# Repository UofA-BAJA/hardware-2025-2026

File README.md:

# hardware-2025-2026
Hardware Branch for 2025-2026 Baja

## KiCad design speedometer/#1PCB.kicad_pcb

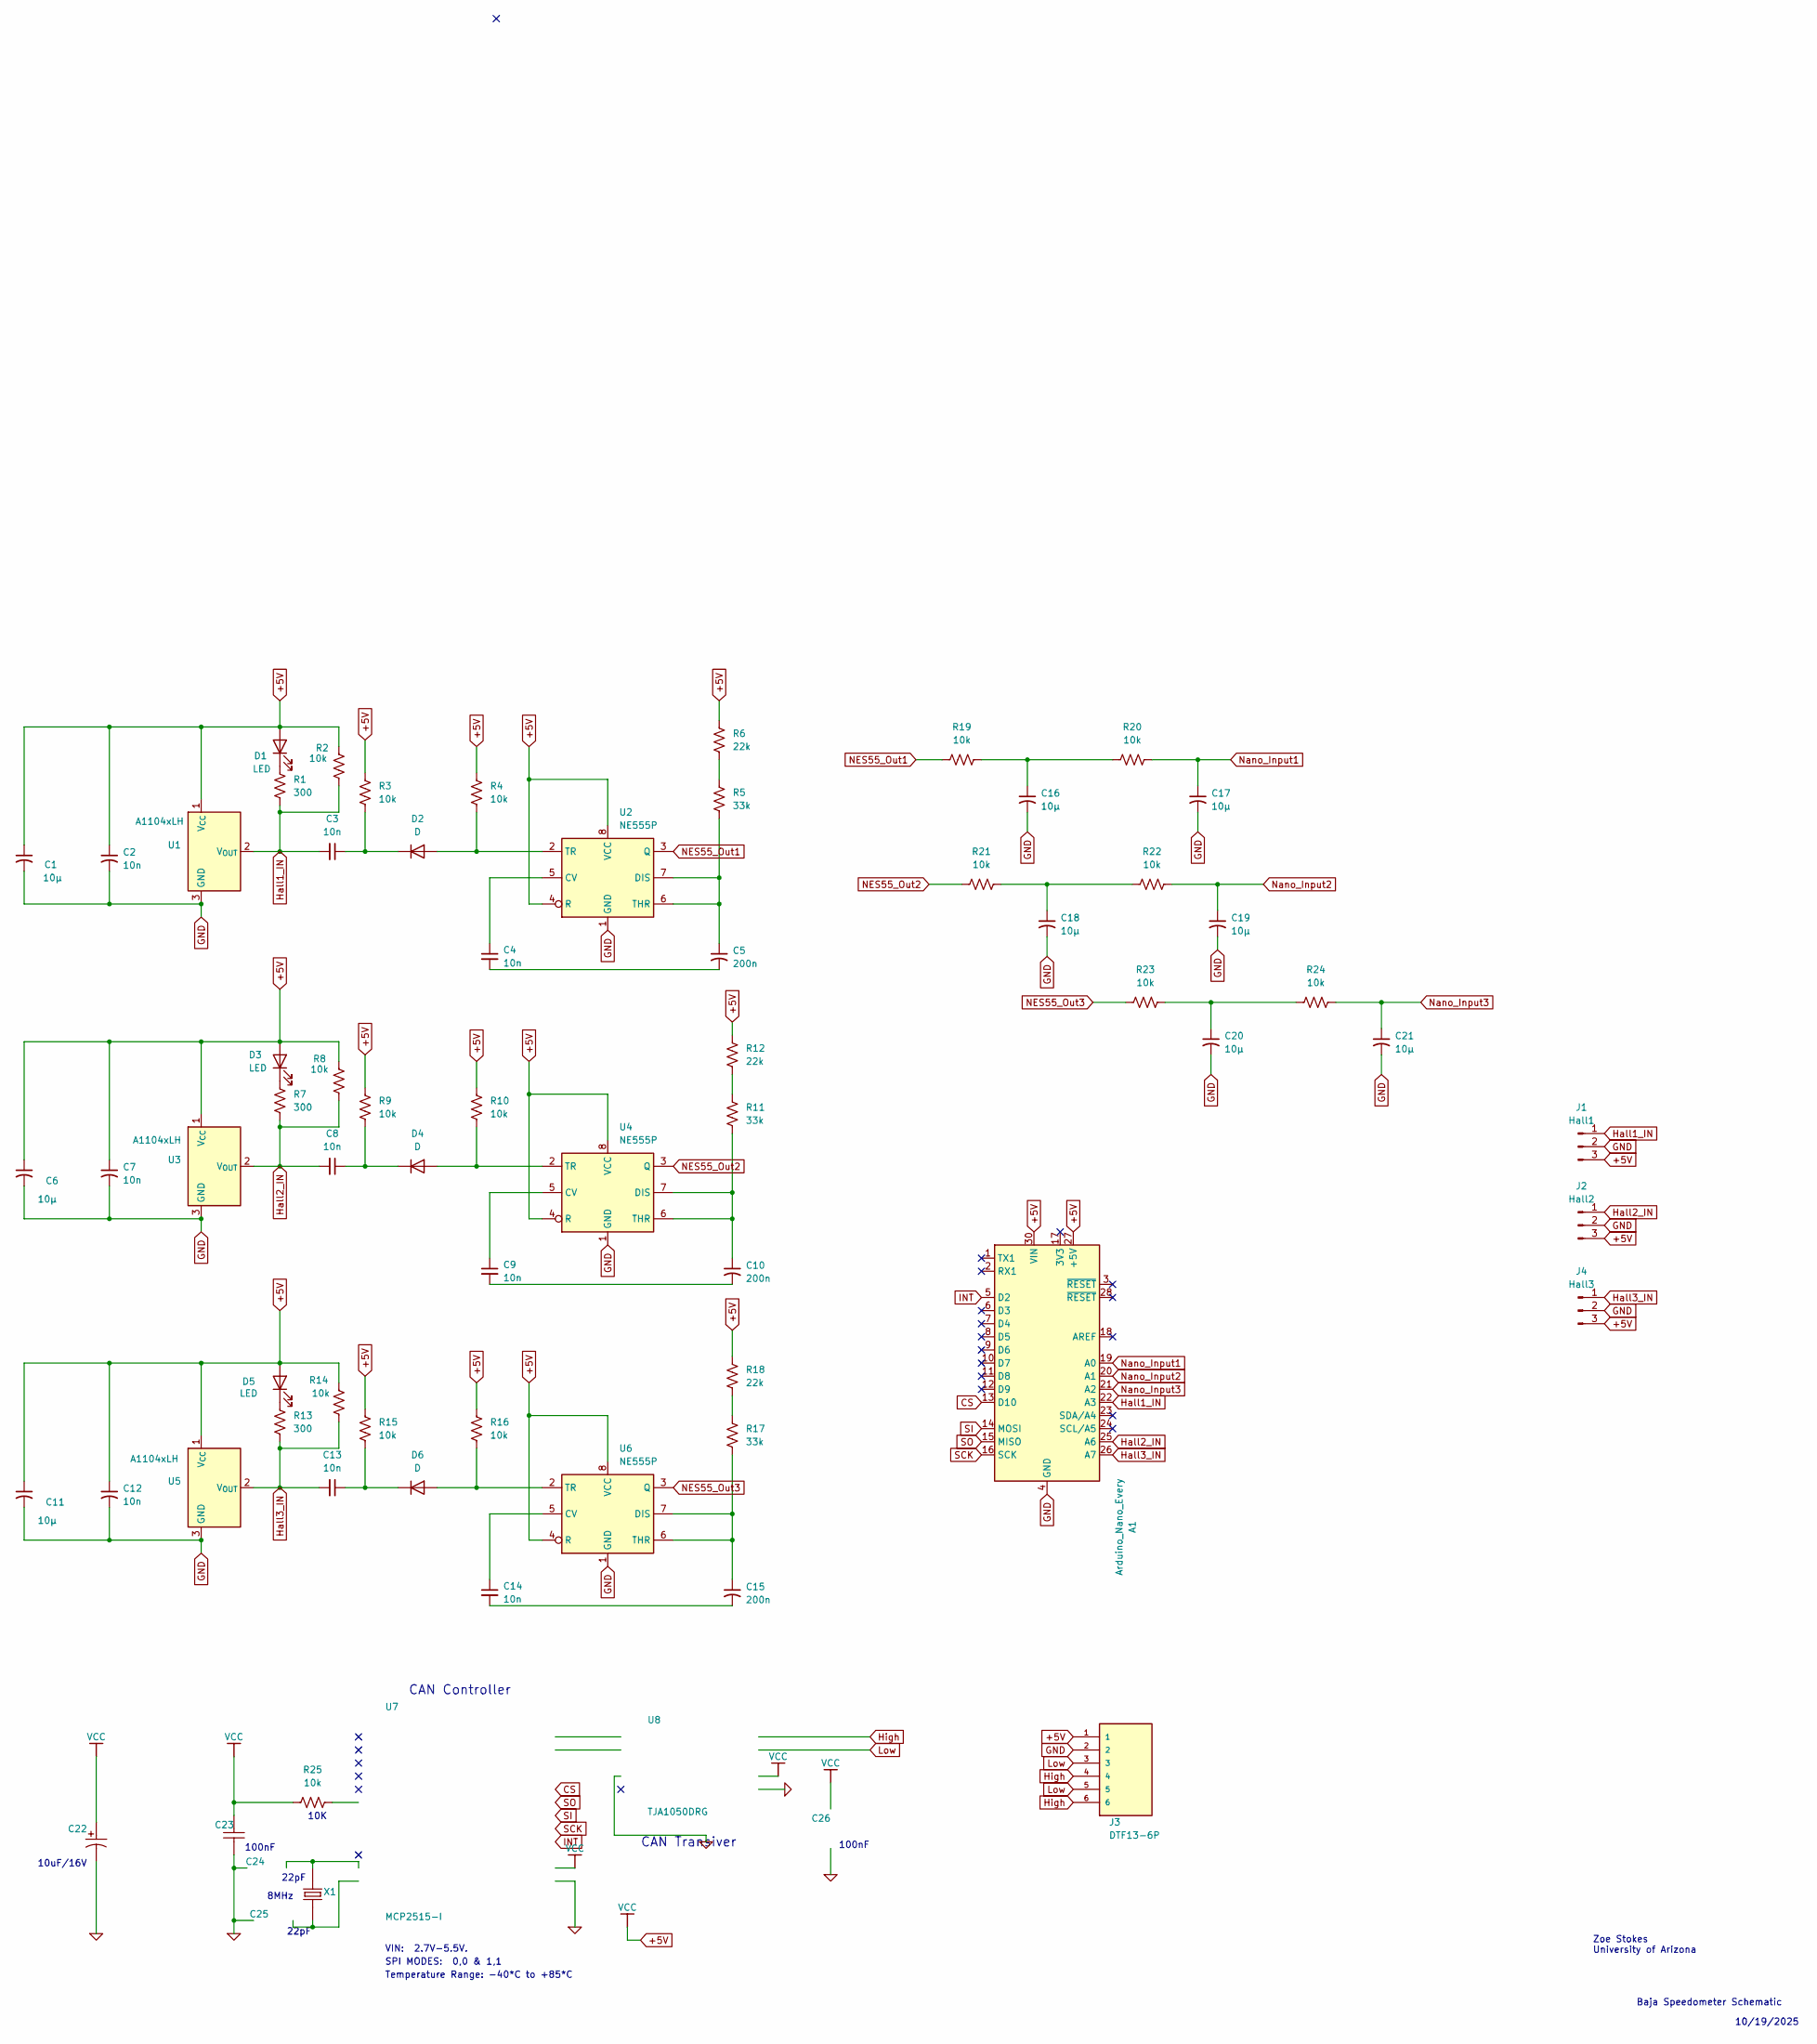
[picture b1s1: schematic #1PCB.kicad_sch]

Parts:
A1: Arduino_Nano_Every; Arduino_Nano
C1, C6, C11, C16, C17, C18, C19, C20, C21: 10µ; CP_Radial_D4.0mm_P2.00mm
C2, C7, C12: 10n; CP_Radial_D4.0mm_P2.00mm
C3, C4, C8, C9, C13, C14: 10n; C_Disc_D3.8mm_W2.6mm_P2.50mm
C5, C10, C15: 200n; CP_Radial_D4.0mm_P2.00mm
C22: 10uF/16V; CP_EIA-1608-08_AVX-J
C23, C26: 100nF; C_0603_1608Metric; PART NUMBER C0603-N.C.
C24, C25: 22pF; C_0603_1608Metric; PART NUMBER C0603-N.C.
D1, D3, D5: LED; LED_D4.0mm
D2, D4, D6: D; D_DO-41_SOD81_P7.62mm_Horizontal
J1: Hall1; PinHeader_1x03_P2.54mm_Vertical
J2: Hall2; PinHeader_1x03_P2.54mm_Vertical
J3: DTF13-6P; TE_DTF13-6P; PARTREV B
J4: Hall3; PinHeader_1x03_P2.54mm_Vertical
R1, R7, R13: 300; R_Axial_DIN0204_L3.6mm_D1.6mm_P7.62mm_Horizontal
R2, R3, R4, R8, R9, R10, R14, R15, R16, R19, R20, R21, R22, R23, R24, R25: 10k; R_Axial_DIN0204_L3.6mm_D1.6mm_P7.62mm_Horizontal
R5, R11, R17: 33k; R_Axial_DIN0204_L3.6mm_D1.6mm_P7.62mm_Horizontal
R6, R12, R18: 22k; R_Axial_DIN0204_L3.6mm_D1.6mm_P7.62mm_Horizontal
U1, U3, U5: A1104xLH; SOT-23W
U2, U4, U6: NE555P; DIP-8_W7.62mm
U7: MCP2515-I; SOIC-18W_7.5x11.6mm_P1.27mm; MANUFACTURER PART MCP2515-I; JLCPCB PART CLASS Extended Part
U8: TJA1050DRG; SOIC-8_5.3x5.3mm_P1.27mm; MANUFACTURER PART TJA1050DRG; LCSC PART NAME TJA1050DRG
X1: 8MHz; Crystal_SMD_HC49-SD

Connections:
0: C22.2, C23.1, C24.2, C25.2, C26.1, U7.9 (VSS), U8.2 (GND), U8.8 (STB)
+5V: A1.27 (+5V), A1.30 (VIN), C1.1, C2.1, C6.1, C7.1, C11.1, C12.1, C22.1, C23.2, C26.2, D1.2 (A), D3.2 (A), D5.2 (A), J1.3, J2.3, J3.1, J4.3, R2.1, R3.1, R4.1, R6.1, R8.1, R9.1, R10.1, R12.1, R14.1, R15.1, R16.1, R18.1, R25.1, U1.1 (V_{CC}), U2.4 (R), U2.8 (VCC), U3.1 (V_{CC}), U4.4 (R), U4.8 (VCC), U5.1 (V_{CC}), U6.4 (R), U6.8 (VCC), U7.18 (VDD), U8.3 (VCC)
CS: A1.13 (D10), U7.16 (~CS)
GND: A1.4 (GND), A1.29 (GND), C1.2, C2.2, C6.2, C7.2, C11.2, C12.2, C16.2, C17.2, C18.2, C19.2, C20.2, C21.2, J1.2, J2.2, J3.2, J4.2, U1.3 (GND), U2.1 (GND), U3.3 (GND), U4.1 (GND), U5.3 (GND), U6.1 (GND)
Hall1_IN: A1.22 (A3), C3.2, J1.1, R1.2, R2.2, U1.2 (V_{OUT})
Hall2_IN: A1.25 (A6), C8.2, J2.1, R7.2, R8.2, U3.2 (V_{OUT})
Hall3_IN: A1.26 (A7), C13.2, J4.1, R13.2, R14.2, U5.2 (V_{OUT})
High: J3.4, J3.6, U8.7 (CANH)
INT: A1.5 (D2), U7.12 (~INT)
Low: J3.3, J3.5, U8.6 (CANL)
NES55_Out1: R19.2, U2.3 (Q)
NES55_Out2: R21.2, U4.3 (Q)
NES55_Out3: R23.2, U6.3 (Q)
Nano_Input1: A1.19 (A0), C17.1, R20.1
Nano_Input2: A1.20 (A1), C19.1, R22.1
Nano_Input3: A1.21 (A2), C21.1, R24.1
unnamed: C4.2, C5.2
unnamed: C9.2, C10.2
unnamed: C14.2, C15.2
unnamed: C16.1, R19.1, R20.2
unnamed: C18.1, R21.1, R22.2
unnamed: C20.1, R23.1, R24.2
unnamed: D1.1 (K), R1.1
unnamed: D2.2 (A), R4.2, U2.2 (TR)
unnamed: C3.1, D2.1 (K), R3.2
unnamed: D3.1 (K), R7.1
unnamed: D4.2 (A), R10.2, U4.2 (TR)
unnamed: C8.1, D4.1 (K), R9.2
unnamed: D5.1 (K), R13.1
unnamed: D6.2 (A), R16.2, U6.2 (TR)
unnamed: C13.1, D6.1 (K), R15.2
unnamed: R5.1, R6.2
unnamed: R11.1, R12.2
unnamed: R17.1, R18.2
unnamed: C4.1, U2.5 (CV)
unnamed: C5.1, R5.2, U2.6 (THR), U2.7 (DIS)
unnamed: C9.1, U4.5 (CV)
unnamed: C10.1, R11.2, U4.6 (THR), U4.7 (DIS)
unnamed: C14.1, U6.5 (CV)
unnamed: C15.1, R17.2, U6.6 (THR), U6.7 (DIS)
unnamed: C25.1, U7.8 (OSC1), X1.1
unnamed: C24.1, U7.7 (OSC2), X1.2
unnamed: U7.2 (RXCAN), U8.4 (RXD)
unnamed: U7.1 (TXCAN), U8.1 (TXD)
unnamed: R25.2, U7.17 (~RESET)
SCK: A1.16 (SCK), U7.13 (SCK)
SI: A1.14 (MOSI), U7.14 (SI)
SO: A1.15 (MISO), U7.15 (SO)

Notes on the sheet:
Zoe Stokes University of Arizona
100nF
Baja Speedometer Schematic
VIN: 2.7V-5.5V.
22pF
CAN Controller
10K
10/19/2025
CAN Transiver
8MHz
Temperature Range: -40*C to +85*C
SPI MODES: 0,0 & 1,1
10uF/16V

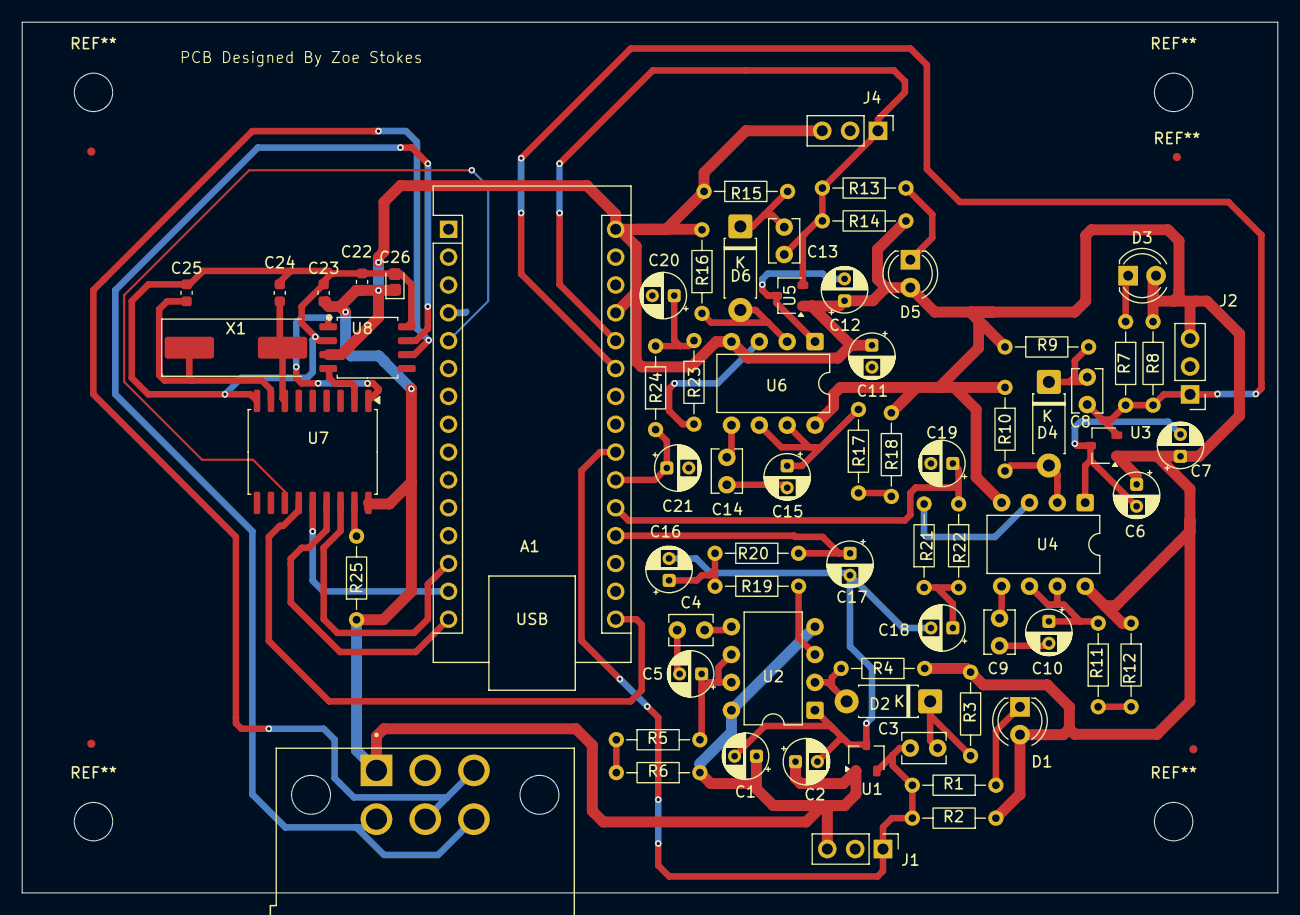
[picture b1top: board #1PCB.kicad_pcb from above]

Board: 2 copper layers, 114.5 x 79.4 mm, 71 parts (0 on the bottom side), 48 nets.

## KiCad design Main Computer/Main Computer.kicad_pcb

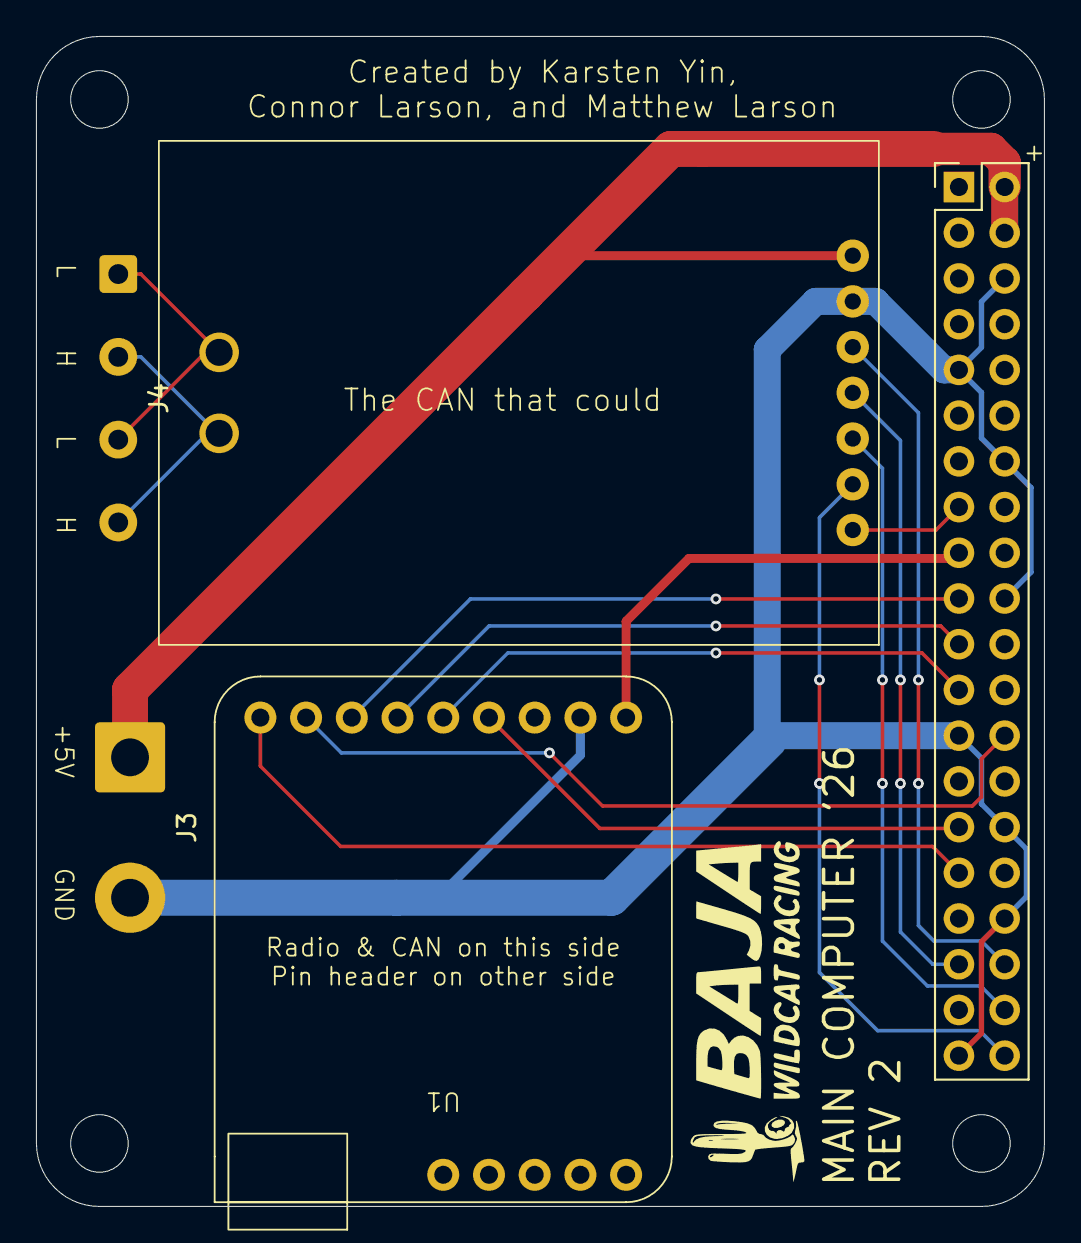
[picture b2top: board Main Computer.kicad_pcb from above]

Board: 2 copper layers, 56.0 x 65.0 mm, 5 parts (0 on the bottom side), 16 nets.

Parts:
J1: Pi 5 GPIO HEADER; PinHeader_2x20_P2.54mm_Vertical
J3: Conn_01x02; SolderWire-1.5sqmm_1x02_P7.8mm_D1.7mm_OD3.9mm
J4: CAN to outer connector; SolderWire-0.5sqmm_1x04_P4.6mm_D0.9mm_OD2.1mm
U1: RFM9X Breakout; Adafruit RFM95W Breakout
UNIT_1: HiLetgo CAN Bus; HiLetgo CAN Bus (Facing Up)

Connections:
3V3: J1.17 (3V3), U1.1 (VIN)
+5v: J1.2 (5V), J1.4 (5V), J3.1, UNIT_1.7 (VCC)
CAN_CS: J1.36 (GPIO_16), UNIT_1.5 (CS)
CAN_INT: J1.15 (GPIO_22), UNIT_1.1 (INT)
CSN: J1.26 (GPIO_7), U1.8 (CS)
GND: J1.6 (GND), J1.9 (GND), J1.14 (GND), J1.20 (GND), J1.25 (GND), J1.30 (GND), J1.34 (GND), J1.39 (GND), J3.2, U1.2 (GND), UNIT_1.6 (GND)
High: J4.2, J4.4, UNIT_1.8 (High_CAN)
Low: J4.1, J4.3, UNIT_1.9 (Low_CAN)
RADIO_INT: J1.29 (GPIO_5), U1.4 (G0_INT)
RST: J1.31 (GPIO_6), U1.9 (RST)
SCK: J1.23 (GPIO_11), U1.5 (SCK)
SI: J1.19 (GPIO_10), U1.7 (MOSI)
SO: J1.21 (GPIO_9), U1.6 (MISO)
SPI1_MISO: J1.35 (GPIO_19), UNIT_1.4 (SO)
SPI1_MOSI: J1.38 (GPIO_20), UNIT_1.3 (SI)
SPI1_SCK: J1.40 (GPIO_21), UNIT_1.2 (SCK)

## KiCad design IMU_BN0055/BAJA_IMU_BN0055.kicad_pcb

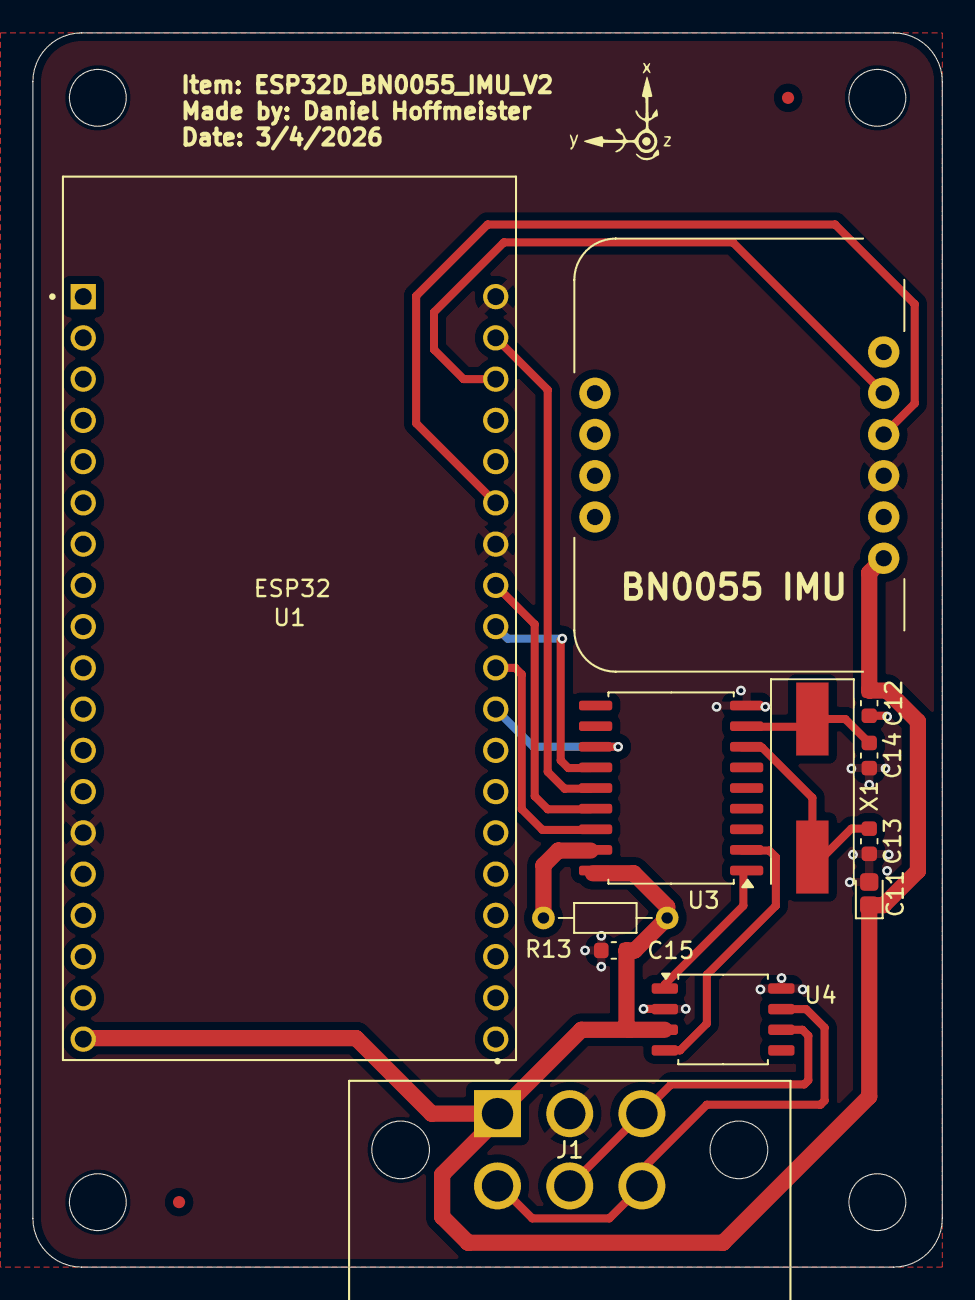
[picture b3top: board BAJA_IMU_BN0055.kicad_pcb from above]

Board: 2 copper layers, 56.0 x 76.0 mm, 12 parts (0 on the bottom side), 16 nets.

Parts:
C11: 10uF/16V; CP_EIA-1608-08_AVX-J
C12, C15: 100nF; C_0603_1608Metric
C13, C14: 22pF; C_0603_1608Metric
J1: DTF13-6P; TE_DTF13-6P
R13: 10k; R_Axial_DIN0204_L3.6mm_D1.6mm_P7.62mm_Horizontal
U1: ESP32-DEVKITC-32D; MODULE_ESP32-DEVKITC-32D
U3: MCP2515-I; SOIC-18W_7.5x11.6mm_P1.27mm
U4: TJA1050DRG; SOIC-8_5.3x5.3mm_P1.27mm
UNIT_1: BNO055; MODULE_2472(BN0055)
X1: 8MHz; Crystal_SMD_HC49-SD

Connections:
0: C11.2, C12.1, C13.2, C14.2, C15.1, J1.2, U1.J2-14 (GND1), U1.J3-1 (GND3), U1.J3-7 (GND2), U3.9 (VSS), U4.2 (GND), U4.8 (STB), UNIT_1.3 (GND)
+5V: C11.1, C12.2, C15.2, J1.1, R13.1, U1.J2-19 (EXT_5V), U3.18 (VDD), U4.3 (VCC), UNIT_1.1 (VIN)
CS: U1.J3-10 (IO5), U3.16 (~CS)
High: J1.4, J1.6, U4.7 (CANH)
Int: U1.J3-11 (IO17), U3.12 (~INT)
Low: J1.3, J1.5, U4.6 (CANL)
unnamed: U1.J3-6 (IO21), UNIT_1.4 (SDA)
unnamed: U1.J3-3 (IO22), UNIT_1.5 (SCL)
unnamed: C14.1, U3.8 (OSC1), X1.1
unnamed: C13.1, U3.7 (OSC2), X1.2
unnamed: U3.2 (RXCAN), U4.4 (RXD)
unnamed: U3.1 (TXCAN), U4.1 (TXD)
unnamed: R13.2, U3.17 (~RESET)
SCK: U1.J3-9 (IO18), U3.13 (SCK)
SI: U1.J3-2 (IO23), U3.14 (SI)
SO: U1.J3-8 (IO19), U3.15 (SO)

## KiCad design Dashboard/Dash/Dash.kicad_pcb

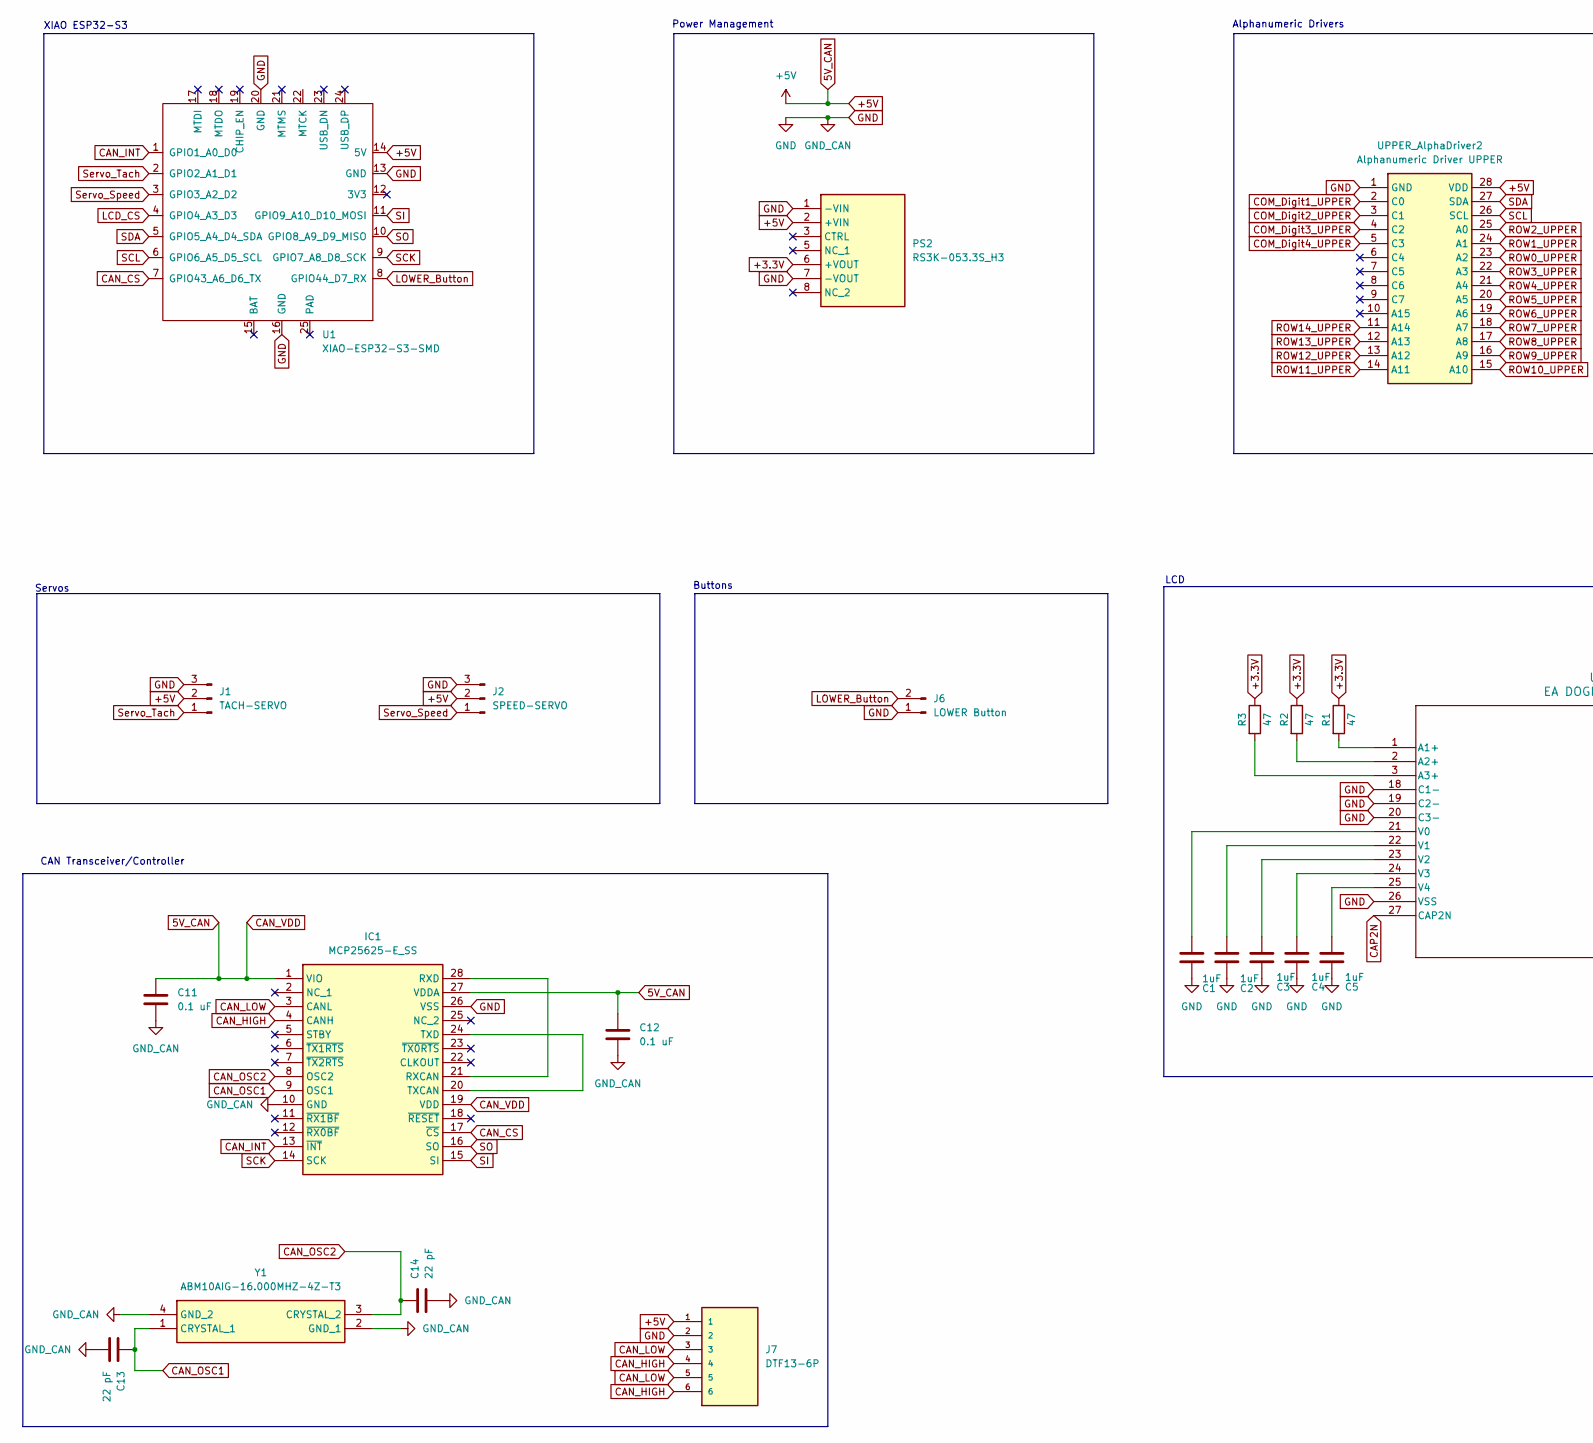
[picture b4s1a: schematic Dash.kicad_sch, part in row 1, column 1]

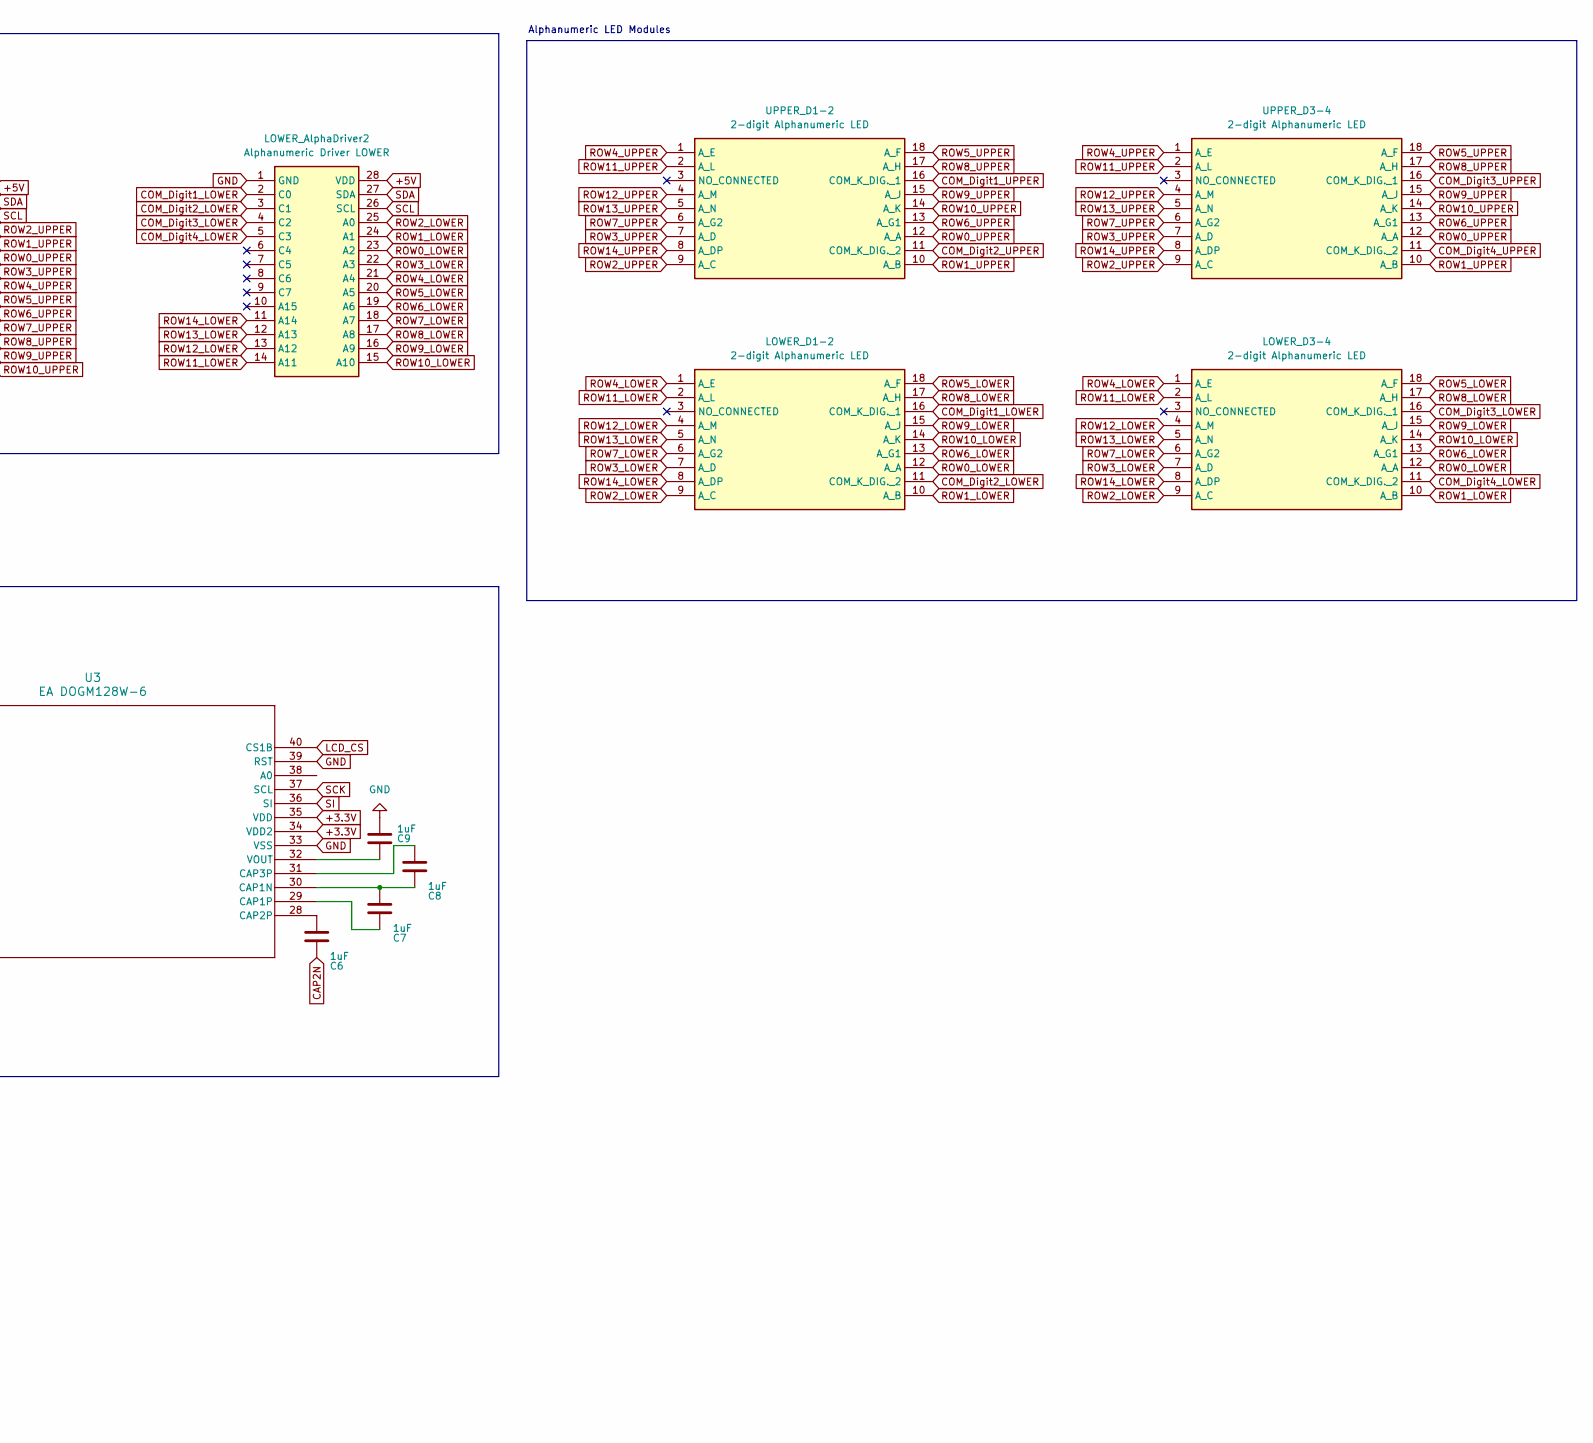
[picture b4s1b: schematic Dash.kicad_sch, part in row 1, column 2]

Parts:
C1, C2, C3, C4, C5, C6, C7, C8, C9: 1uF; CAPC1608X90
C11, C12: 0.1 uF; CAPC0603X35N
C13, C14: 22 pF; CAPC1608X87N
IC1: MCP25625-E_SS; SOP65P780X200-28N; Manufacturer_Part_Number MCP25625-E/SS; Mouser Part Number 579-MCP25625-E/SS
J1: TACH-SERVO; PinHeader_1x03_P2.54mm_Vertical
J2: SPEED-SERVO; PinHeader_1x03_P2.54mm_Vertical
J6: LOWER Button; PinHeader_1x02_P2.54mm_Vertical
J7: DTF13-6P; TE_DTF13-6P; PARTREV B
LOWER_AlphaDriver2: Alphanumeric Driver LOWER; DIP1778W100P254L3556H630Q28N; Manufacturer_Part_Number 1427; Mouser Part Number 485-1427
LOWER_D1-2, LOWER_D3-4: 2-digit Alphanumeric LED; 1908; Manufacturer_Part_Number 1908; Mouser Part Number 485-1908
PS2: RS3K-053.3S_H3; RS3K0533SH3; Manufacturer_Part_Number RS3K-053.3S/H3; Mouser Part Number 919-RS3K-053.3S/H3
R1, R2, R3: 47; RESC2012X65N
U1: XIAO-ESP32-S3-SMD; XIAO-ESP32S3-SMD
U3: EA DOGM128W-6; EA_DOGM128-6
UPPER_AlphaDriver2: Alphanumeric Driver UPPER; DIP1778W100P254L3556H630Q28N; Manufacturer_Part_Number 1427; Mouser Part Number 485-1427
UPPER_D1-2, UPPER_D3-4: 2-digit Alphanumeric LED; 1908; Manufacturer_Part_Number 1908; Mouser Part Number 485-1908
Y1: ABM10AIG-16.000MHZ-4Z-T3; ABM10AIG16000MHZ4ZT3; Manufacturer_Part_Number ABM10AIG-16.000MHZ-4Z-T3; Mouser Part Number 815-M10AIG-16-4ZT3

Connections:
+3.3V: PS2.6 (+VOUT), R1.1, R2.1, R3.1, U3.34 (VDD2), U3.35 (VDD)
+5V: C11.1, C12.1, IC1.1 (VIO), IC1.19 (VDD), IC1.27 (VDDA), J1.2, J2.2, J7.1, LOWER_AlphaDriver2.28 (VDD), PS2.2 (+VIN), U1.14 (5V), UPPER_AlphaDriver2.28 (VDD); also elsewhere on the board
CAN_CS: IC1.17 (~CS), U1.7 (GPIO43_A6_D6_TX)
CAN_HIGH: IC1.4 (CANH), J7.4, J7.6
CAN_INT: IC1.13 (~INT), U1.1 (GPIO1_A0_D0)
CAN_LOW: IC1.3 (CANL), J7.3, J7.5
CAN_OSC1: C13.1, IC1.9 (OSC1), Y1.1 (CRYSTAL_1)
CAN_OSC2: C14.1, IC1.8 (OSC2), Y1.3 (CRYSTAL_2)
CAP2N: C6.1, U3.27 (CAP2N)
COM_Digit1_LOWER: LOWER_AlphaDriver2.2 (C0), LOWER_D1-2.16 (COM_K_DIG._1); also elsewhere on the board
COM_Digit1_UPPER: UPPER_AlphaDriver2.2 (C0), UPPER_D1-2.16 (COM_K_DIG._1); also elsewhere on the board
COM_Digit2_LOWER: LOWER_AlphaDriver2.3 (C1), LOWER_D1-2.11 (COM_K_DIG._2); also elsewhere on the board
COM_Digit2_UPPER: UPPER_AlphaDriver2.3 (C1), UPPER_D1-2.11 (COM_K_DIG._2); also elsewhere on the board
COM_Digit3_LOWER: LOWER_AlphaDriver2.4 (C2), LOWER_D3-4.16 (COM_K_DIG._1); also elsewhere on the board
COM_Digit3_UPPER: UPPER_AlphaDriver2.4 (C2), UPPER_D3-4.16 (COM_K_DIG._1); also elsewhere on the board
COM_Digit4_LOWER: LOWER_AlphaDriver2.5 (C3), LOWER_D3-4.11 (COM_K_DIG._2); also elsewhere on the board
COM_Digit4_UPPER: UPPER_AlphaDriver2.5 (C3), UPPER_D3-4.11 (COM_K_DIG._2); also elsewhere on the board
GND: C1.1, C2.1, C3.1, C4.1, C5.1, C9.2, C11.2, C12.2, C13.2, C14.2, IC1.10 (GND), IC1.26 (VSS), J1.3, J2.3, J6.1, J7.2, LOWER_AlphaDriver2.1 (GND), PS2.1 (-VIN), PS2.7 (-VOUT), U1.13 (GND), U1.16 (GND), U1.20 (GND), U3.18 (C1-), U3.19 (C2-), U3.20 (C3-), U3.26 (VSS), U3.33 (VSS), U3.39 (RST), UPPER_AlphaDriver2.1 (GND), Y1.2 (GND_1), Y1.4 (GND_2); also elsewhere on the board
LCD_CS: U1.4 (GPIO4_A3_D3), U3.40 (CS1B)
LOWER_Button: J6.2, U1.8 (GPIO44_D7_RX)
unnamed: IC1.21 (RXCAN), IC1.28 (RXD)
unnamed: IC1.20 (TXCAN), IC1.24 (TXD)
unnamed: R1.2, U3.1 (A1+)
unnamed: R2.2, U3.2 (A2+)
unnamed: R3.2, U3.3 (A3+)
unnamed: C7.2, C8.1, U3.30 (CAP1N)
unnamed: C7.1, U3.29 (CAP1P)
unnamed: C6.2, U3.28 (CAP2P)
unnamed: C8.2, U3.31 (CAP3P)
unnamed: C1.2, U3.21 (V0)
unnamed: C2.2, U3.22 (V1)
unnamed: C3.2, U3.23 (V2)
unnamed: C4.2, U3.24 (V3)
unnamed: C5.2, U3.25 (V4)
unnamed: C9.1, U3.32 (VOUT)
ROW0_LOWER: LOWER_AlphaDriver2.23 (A2), LOWER_D1-2.12 (A_A), LOWER_D3-4.12 (A_A); also elsewhere on the board
ROW0_UPPER: UPPER_AlphaDriver2.23 (A2), UPPER_D1-2.12 (A_A), UPPER_D3-4.12 (A_A); also elsewhere on the board
ROW1_LOWER: LOWER_AlphaDriver2.24 (A1), LOWER_D1-2.10 (A_B), LOWER_D3-4.10 (A_B); also elsewhere on the board
ROW1_UPPER: UPPER_AlphaDriver2.24 (A1), UPPER_D1-2.10 (A_B), UPPER_D3-4.10 (A_B); also elsewhere on the board
ROW2_LOWER: LOWER_AlphaDriver2.25 (A0), LOWER_D1-2.9 (A_C), LOWER_D3-4.9 (A_C); also elsewhere on the board
ROW2_UPPER: UPPER_AlphaDriver2.25 (A0), UPPER_D1-2.9 (A_C), UPPER_D3-4.9 (A_C); also elsewhere on the board
ROW3_LOWER: LOWER_AlphaDriver2.22 (A3), LOWER_D1-2.7 (A_D), LOWER_D3-4.7 (A_D); also elsewhere on the board
ROW3_UPPER: UPPER_AlphaDriver2.22 (A3), UPPER_D1-2.7 (A_D), UPPER_D3-4.7 (A_D); also elsewhere on the board
ROW4_LOWER: LOWER_AlphaDriver2.21 (A4), LOWER_D1-2.1 (A_E), LOWER_D3-4.1 (A_E); also elsewhere on the board
ROW4_UPPER: UPPER_AlphaDriver2.21 (A4), UPPER_D1-2.1 (A_E), UPPER_D3-4.1 (A_E); also elsewhere on the board
ROW5_LOWER: LOWER_AlphaDriver2.20 (A5), LOWER_D1-2.18 (A_F), LOWER_D3-4.18 (A_F); also elsewhere on the board
ROW5_UPPER: UPPER_AlphaDriver2.20 (A5), UPPER_D1-2.18 (A_F), UPPER_D3-4.18 (A_F); also elsewhere on the board
ROW6_LOWER: LOWER_AlphaDriver2.19 (A6), LOWER_D1-2.13 (A_G1), LOWER_D3-4.13 (A_G1); also elsewhere on the board
ROW6_UPPER: UPPER_AlphaDriver2.19 (A6), UPPER_D1-2.13 (A_G1), UPPER_D3-4.13 (A_G1); also elsewhere on the board
ROW7_LOWER: LOWER_AlphaDriver2.18 (A7), LOWER_D1-2.6 (A_G2), LOWER_D3-4.6 (A_G2); also elsewhere on the board
ROW7_UPPER: UPPER_AlphaDriver2.18 (A7), UPPER_D1-2.6 (A_G2), UPPER_D3-4.6 (A_G2); also elsewhere on the board
ROW8_LOWER: LOWER_AlphaDriver2.17 (A8), LOWER_D1-2.17 (A_H), LOWER_D3-4.17 (A_H); also elsewhere on the board
ROW8_UPPER: UPPER_AlphaDriver2.17 (A8), UPPER_D1-2.17 (A_H), UPPER_D3-4.17 (A_H); also elsewhere on the board
ROW9_LOWER: LOWER_AlphaDriver2.16 (A9), LOWER_D1-2.15 (A_J), LOWER_D3-4.15 (A_J); also elsewhere on the board
ROW9_UPPER: UPPER_AlphaDriver2.16 (A9), UPPER_D1-2.15 (A_J), UPPER_D3-4.15 (A_J); also elsewhere on the board
ROW10_LOWER: LOWER_AlphaDriver2.15 (A10), LOWER_D1-2.14 (A_K), LOWER_D3-4.14 (A_K); also elsewhere on the board
ROW10_UPPER: UPPER_AlphaDriver2.15 (A10), UPPER_D1-2.14 (A_K), UPPER_D3-4.14 (A_K); also elsewhere on the board
ROW11_LOWER: LOWER_AlphaDriver2.14 (A11), LOWER_D1-2.2 (A_L), LOWER_D3-4.2 (A_L); also elsewhere on the board
ROW11_UPPER: UPPER_AlphaDriver2.14 (A11), UPPER_D1-2.2 (A_L), UPPER_D3-4.2 (A_L); also elsewhere on the board
ROW12_LOWER: LOWER_AlphaDriver2.13 (A12), LOWER_D1-2.4 (A_M), LOWER_D3-4.4 (A_M); also elsewhere on the board
ROW12_UPPER: UPPER_AlphaDriver2.13 (A12), UPPER_D1-2.4 (A_M), UPPER_D3-4.4 (A_M); also elsewhere on the board
ROW13_LOWER: LOWER_AlphaDriver2.12 (A13), LOWER_D1-2.5 (A_N), LOWER_D3-4.5 (A_N); also elsewhere on the board
ROW13_UPPER: UPPER_AlphaDriver2.12 (A13), UPPER_D1-2.5 (A_N), UPPER_D3-4.5 (A_N); also elsewhere on the board
ROW14_LOWER: LOWER_AlphaDriver2.11 (A14), LOWER_D1-2.8 (A_DP), LOWER_D3-4.8 (A_DP); also elsewhere on the board
ROW14_UPPER: UPPER_AlphaDriver2.11 (A14), UPPER_D1-2.8 (A_DP), UPPER_D3-4.8 (A_DP); also elsewhere on the board
SCK: IC1.14 (SCK), U1.9 (GPIO7_A8_D8_SCK), U3.37 (SCL)
SCL: LOWER_AlphaDriver2.26 (SCL), U1.6 (GPIO6_A5_D5_SCL), UPPER_AlphaDriver2.26 (SCL); also elsewhere on the board
SDA: LOWER_AlphaDriver2.27 (SDA), U1.5 (GPIO5_A4_D4_SDA), UPPER_AlphaDriver2.27 (SDA); also elsewhere on the board
SI: IC1.15 (SI), U1.11 (GPIO9_A10_D10_MOSI), U3.36 (SI)
SO: IC1.16 (SO), U1.10 (GPIO8_A9_D9_MISO)
Servo_Speed: J2.1, U1.3 (GPIO3_A2_D2)
Servo_Tach: J1.1, U1.2 (GPIO2_A1_D1)

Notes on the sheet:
Alphanumeric Drivers
LCD
Power Management
Buttons
CAN Transceiver/Controller
Alphanumeric LED Modules
Servos
XIAO ESP32-S3
